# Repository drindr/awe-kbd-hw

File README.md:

# AWE keyboard

awe is a random string without any special meaning 🤪  
awe is highly inspired by [Sweep](https://github.com/davidphilipbarr/Sweep)  

## featues
BLE support by Nrf52840 board([Nice!Nano variant](https://item.taobao.com/item.htm?id=714225655665))  
34~36 keys (2 optional 5-pin joystick socket)  
display (nice!view compatible)  
the PCB is reversible to make it cheaper 😭

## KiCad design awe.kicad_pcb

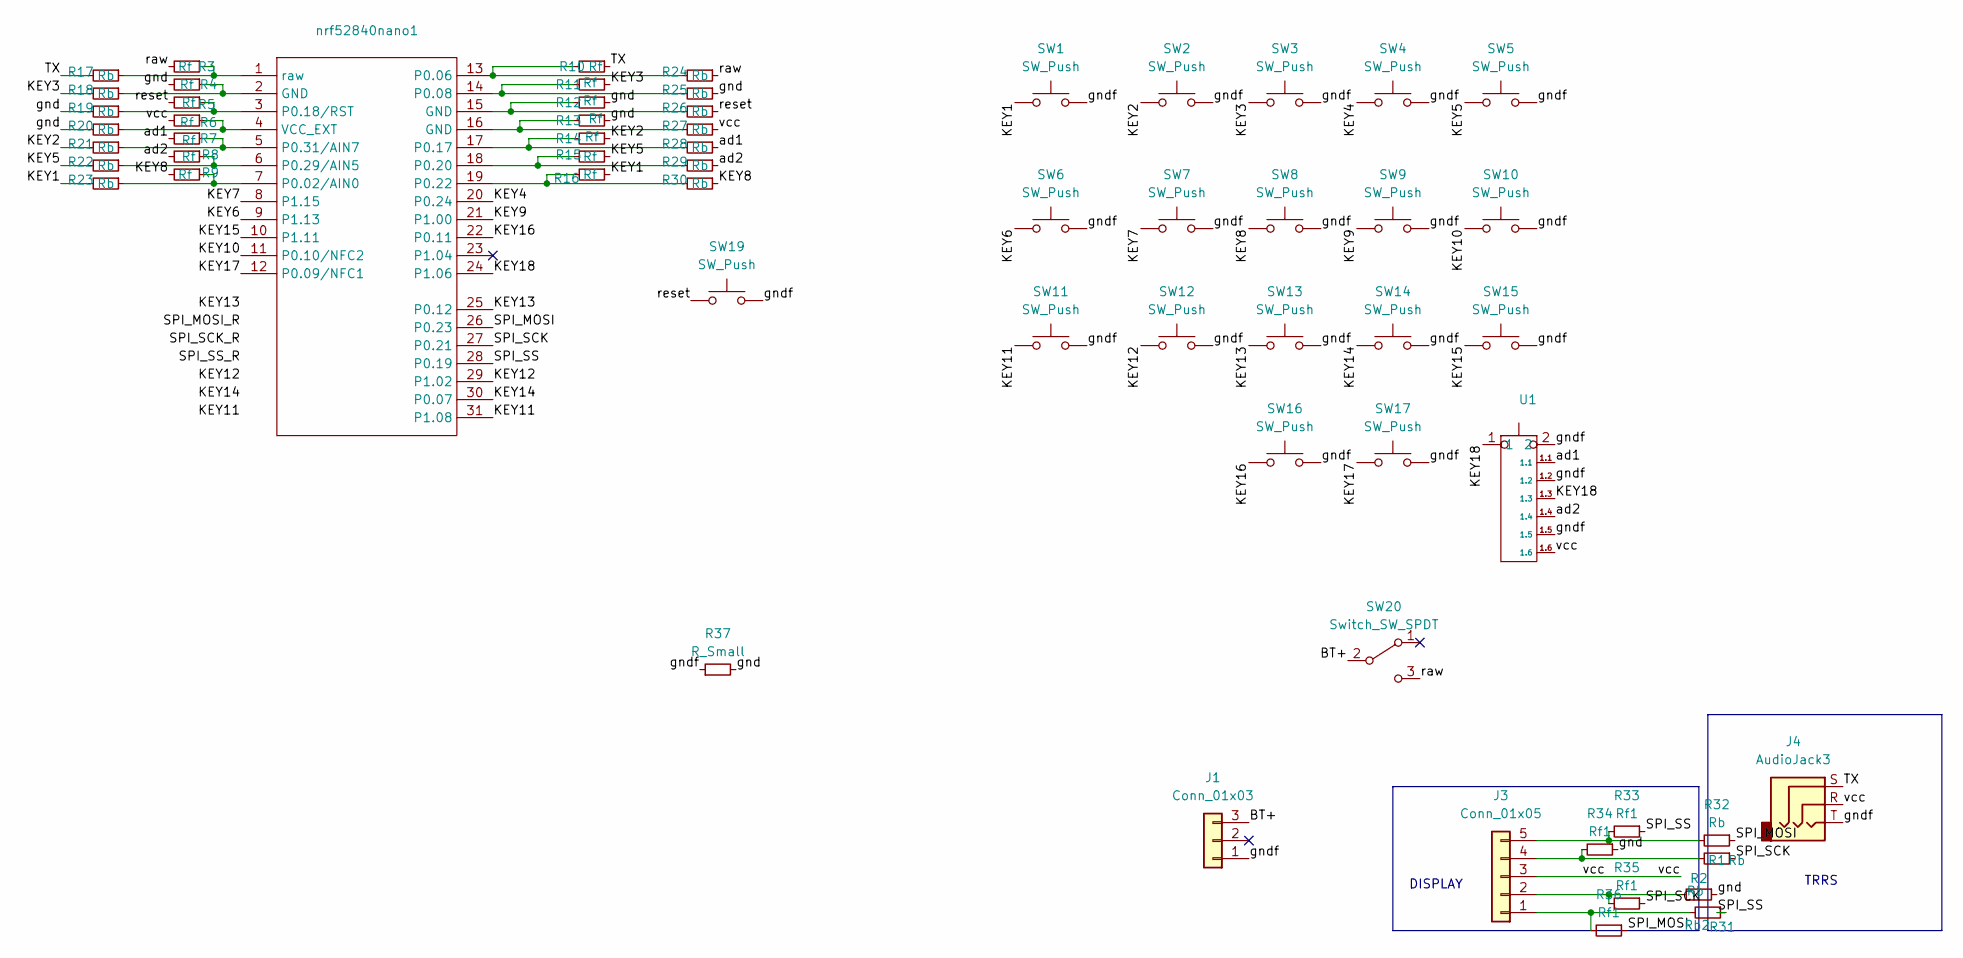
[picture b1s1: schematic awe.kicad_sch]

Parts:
J1: Conn_01x03; xunpu_mx_1.25_3p
J3: Conn_01x05; PinHeader_1x05_P2.54mm_Vertical
J4: AudioJack3; TRRS-PJ-320A-swap
R1, R2, R32: Rb; 0r
R3, R4, R5, R6, R7, R8, R9, R10, R11, R12, R13, R14, R15, R16: Rf; 0r
R17, R18, R19, R20, R21, R22, R23, R24, R25, R26, R27, R28, R29, R30: Rb; 0r_reverse
R31: Rb2; 0r
R33, R34, R35, R36: Rf1; 0r
R37: R_Small; 0r
SW1, SW2, SW3, SW4, SW5, SW6, SW7, SW8, SW9, SW10, SW11, SW12, SW13, SW14, SW15, SW16, SW17: SW_Push; keyswitch_choc12_hotswap_1u_swap
SW19: SW_Push; SW_SPST_B3U-1000P
SW20: Switch_SW_SPDT; SPDT_C128955
U1: keyswitch_choc12_hotswap_1u_swap_joy
nrf52840nano1: 52840NANO_V2_swap

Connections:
/BT+: J1.3, SW20.2 (B)
/KEY1: R16.1, R23.2, SW1.1
/KEY2: R14.1, R21.2, SW2.1
/KEY3: R11.1, R18.2, SW3.1
/KEY4: SW4.1, nrf52840nano1.20 (P0.24)
/KEY5: R15.1, R22.2, SW5.1
/KEY6: SW6.1, nrf52840nano1.9 (P1.13)
/KEY7: SW7.1, nrf52840nano1.8 (P1.15)
/KEY8: R9.2, R30.1, SW8.1
/KEY9: SW9.1, nrf52840nano1.21 (P1.00)
/KEY10: SW10.1, nrf52840nano1.11 (P0.10/NFC2)
/KEY11: SW11.1, nrf52840nano1.31 (P1.08)
/KEY12: SW12.1, nrf52840nano1.29 (P1.02)
/KEY13: SW13.1, nrf52840nano1.25 (P0.12)
/KEY14: SW14.1, nrf52840nano1.30 (P0.07)
/KEY15: SW15.1, nrf52840nano1.10 (P1.11)
/KEY16: SW16.1, nrf52840nano1.22 (P0.11)
/KEY17: SW17.1, nrf52840nano1.12 (P0.09/NFC1)
/KEY18: U1.1, U1.1.3, nrf52840nano1.24 (P1.06)
/SPI_MOSI: R32.1, R36.1, nrf52840nano1.26 (P0.23)
/SPI_SCK: R1.1, R35.1, nrf52840nano1.27 (P0.21)
/SPI_SS: R31.1, R33.1, nrf52840nano1.28 (P0.19)
/TX: J4.S, R10.1, R17.2
/ad1: R7.2, R28.1, U1.1.1
/ad2: R8.2, R29.1, U1.1.4
/gnd: R2.1, R4.2, R12.1, R13.1, R19.2, R20.2, R25.1, R34.1, R37.2; also elsewhere on the board
/gndf: J1.1, J4.T, R37.1, SW1.2, SW2.2, SW3.2, SW4.2, SW5.2, SW6.2, SW7.2, SW8.2, SW9.2, SW10.2, SW11.2, SW12.2, SW13.2, SW14.2, SW15.2, SW16.2, SW17.2, SW19.2, U1.1.2, U1.1.5, U1.2; also elsewhere on the board
/raw: R3.2, R24.1, SW20.3 (C)
/reset: R5.2, R26.1, SW19.1
/vcc: J3.3, J4.R, R6.2, R27.1, U1.1.6
unnamed: J3.1, R31.2, R36.2
unnamed: J3.2, R2.2, R35.2
unnamed: J3.4, R1.2, R34.2
unnamed: J3.5, R32.2, R33.2
unnamed: R12.2, R26.2, nrf52840nano1.15 (GND)
unnamed: R13.2, R27.2, nrf52840nano1.16 (GND)
unnamed: R4.1, R18.1, nrf52840nano1.2 (GND)
unnamed: R9.1, R23.1, nrf52840nano1.7 (P0.02/AIN0)
unnamed: R10.2, R24.2, nrf52840nano1.13 (P0.06)
unnamed: R11.2, R25.2, nrf52840nano1.14 (P0.08)
unnamed: R14.2, R28.2, nrf52840nano1.17 (P0.17)
unnamed: R5.1, R19.1, nrf52840nano1.3 (P0.18/RST)
unnamed: R15.2, R29.2, nrf52840nano1.18 (P0.20)
unnamed: R16.2, R30.2, nrf52840nano1.19 (P0.22)
unnamed: R8.1, R22.1, nrf52840nano1.6 (P0.29/AIN5)
unnamed: R7.1, R21.1, nrf52840nano1.5 (P0.31/AIN7)
unnamed: R6.1, R20.1, nrf52840nano1.4 (VCC_EXT)
unnamed: R3.1, R17.1, nrf52840nano1.1 (raw)

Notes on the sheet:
DISPLAY
TRRS

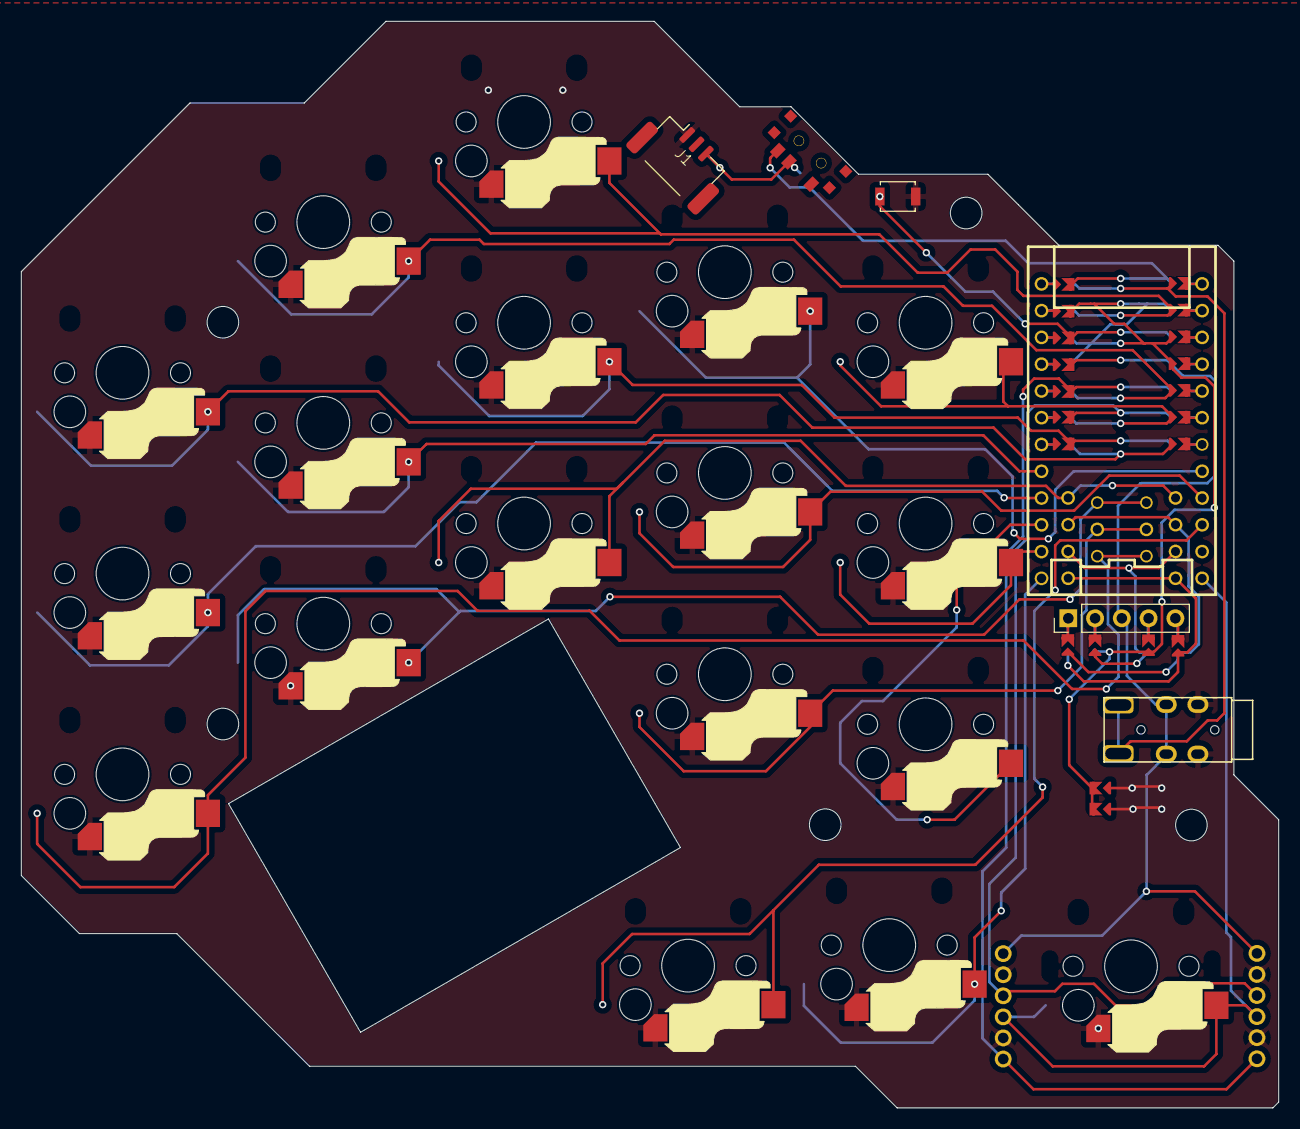
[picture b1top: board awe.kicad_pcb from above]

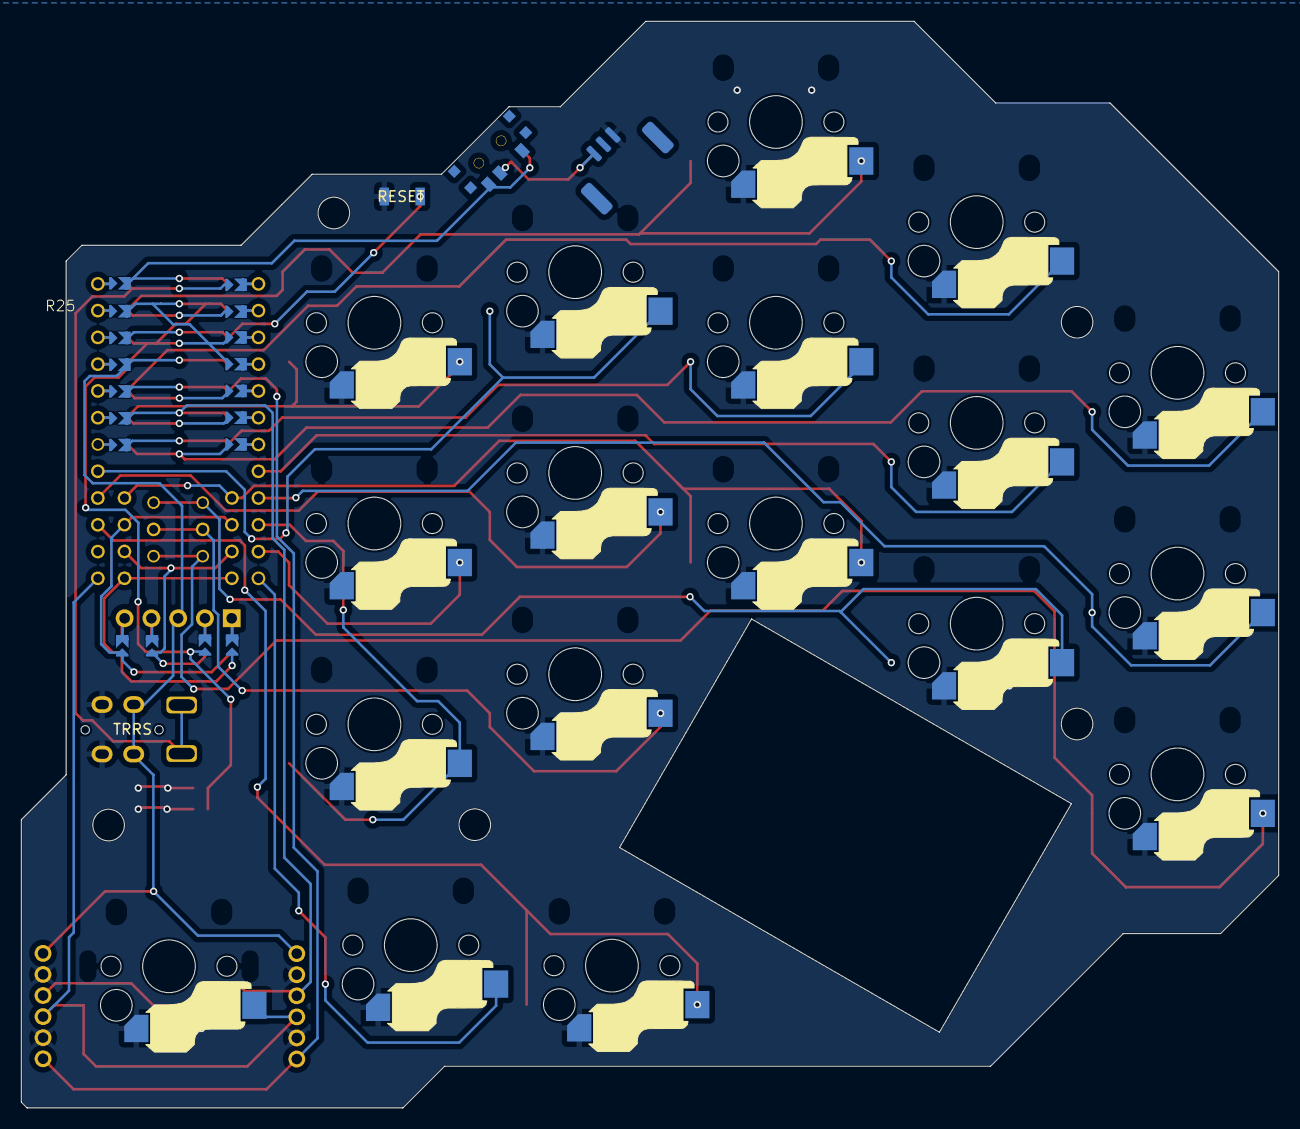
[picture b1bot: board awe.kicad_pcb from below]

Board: 2 copper layers, 119.3 x 103.1 mm, 62 parts (18 on the bottom side), 48 nets.

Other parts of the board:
R37#2: R_Small; 0r

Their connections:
/gnd: R37#2.2; also elsewhere on the board
/gndf: R37#2.1; also elsewhere on the board

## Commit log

2025-03-02 init the repo
